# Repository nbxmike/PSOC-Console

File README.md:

# PSOC-Console

This is an expansion of the operator console for FIRST Robotic Competitions
originally published on the Cypress Semiconductor website:
  https://community.cypress.com/thread/30090
based on the CY8CKIT-059 development board.  I had previously released hardware
to ease the creation of the console, publised on the Cypress website:
  https://community.cypress.com/thread/30074
  
With this project, the Cypress GPL code is being replaced with MIT licensed 
firmware which runs as a task under FreeRTOS 10 (which is licensed under MIT
terms and hence the new firmware being released under the same license.)  The
firmware is not a port, it is new code which has at best been inspired by the
Cypress code meantioned above

The hardware is at the moment (11/OCT/2018) the same as was previously released
hardware.  A new revision of the hardware has been designed to incorporate a
3.3V regulator to make interfacing to PS/2, GameCube and other game console 
devices much easier.  It is entirely possible to interface the existing board
to 3.3V devices, and it has been done, it has been a painful kludge of wires
and ICs glued in place.  Expect updated hardware in the August 2018 timeframe
(boards are out for fab as I write.)

The project has been assigned the USB ID of 0x1d50 | 0x6131 by the 
openmoko USB OUI program.  Anticipating the hardware revision to 3.3V and its
associated updated firmware, a second ID is reserved.  Obtaining unique USB
IDs makes custom host support much easier should something other than stock
HID drivers be desired at some future point.

The project is broken down into three directories:
  Kicad - this folder includes the Kicad source files, gerbers, BOMs, etc.
    Kicad is a free schematic capture package the equal of many commercial
	packages but as FOSS it places no restrictions on use of its outputs.
  PSOC-Creator - This is the source for the firware and PLD of the CPU core
    used for this project.  PSOC Creator is a free integrated development
	enviroment which is not open source nor available for a package other than
	Windows.  It sucks that to use Cypress hardware you are forced into such
	a crap desktop but Cypress does not seem to care too much.
  Documents - I have collected a number for reference documents that I have
    included in this folder.  Should a copyright holder ask that I not provide
	people this information source I will attempt to find open documents to 
	replace them.
	
Licensing:
  Hardware - CERN
  Firmware - MIT
  Documents - individual terms are in each document
  
Enjoy

Mike

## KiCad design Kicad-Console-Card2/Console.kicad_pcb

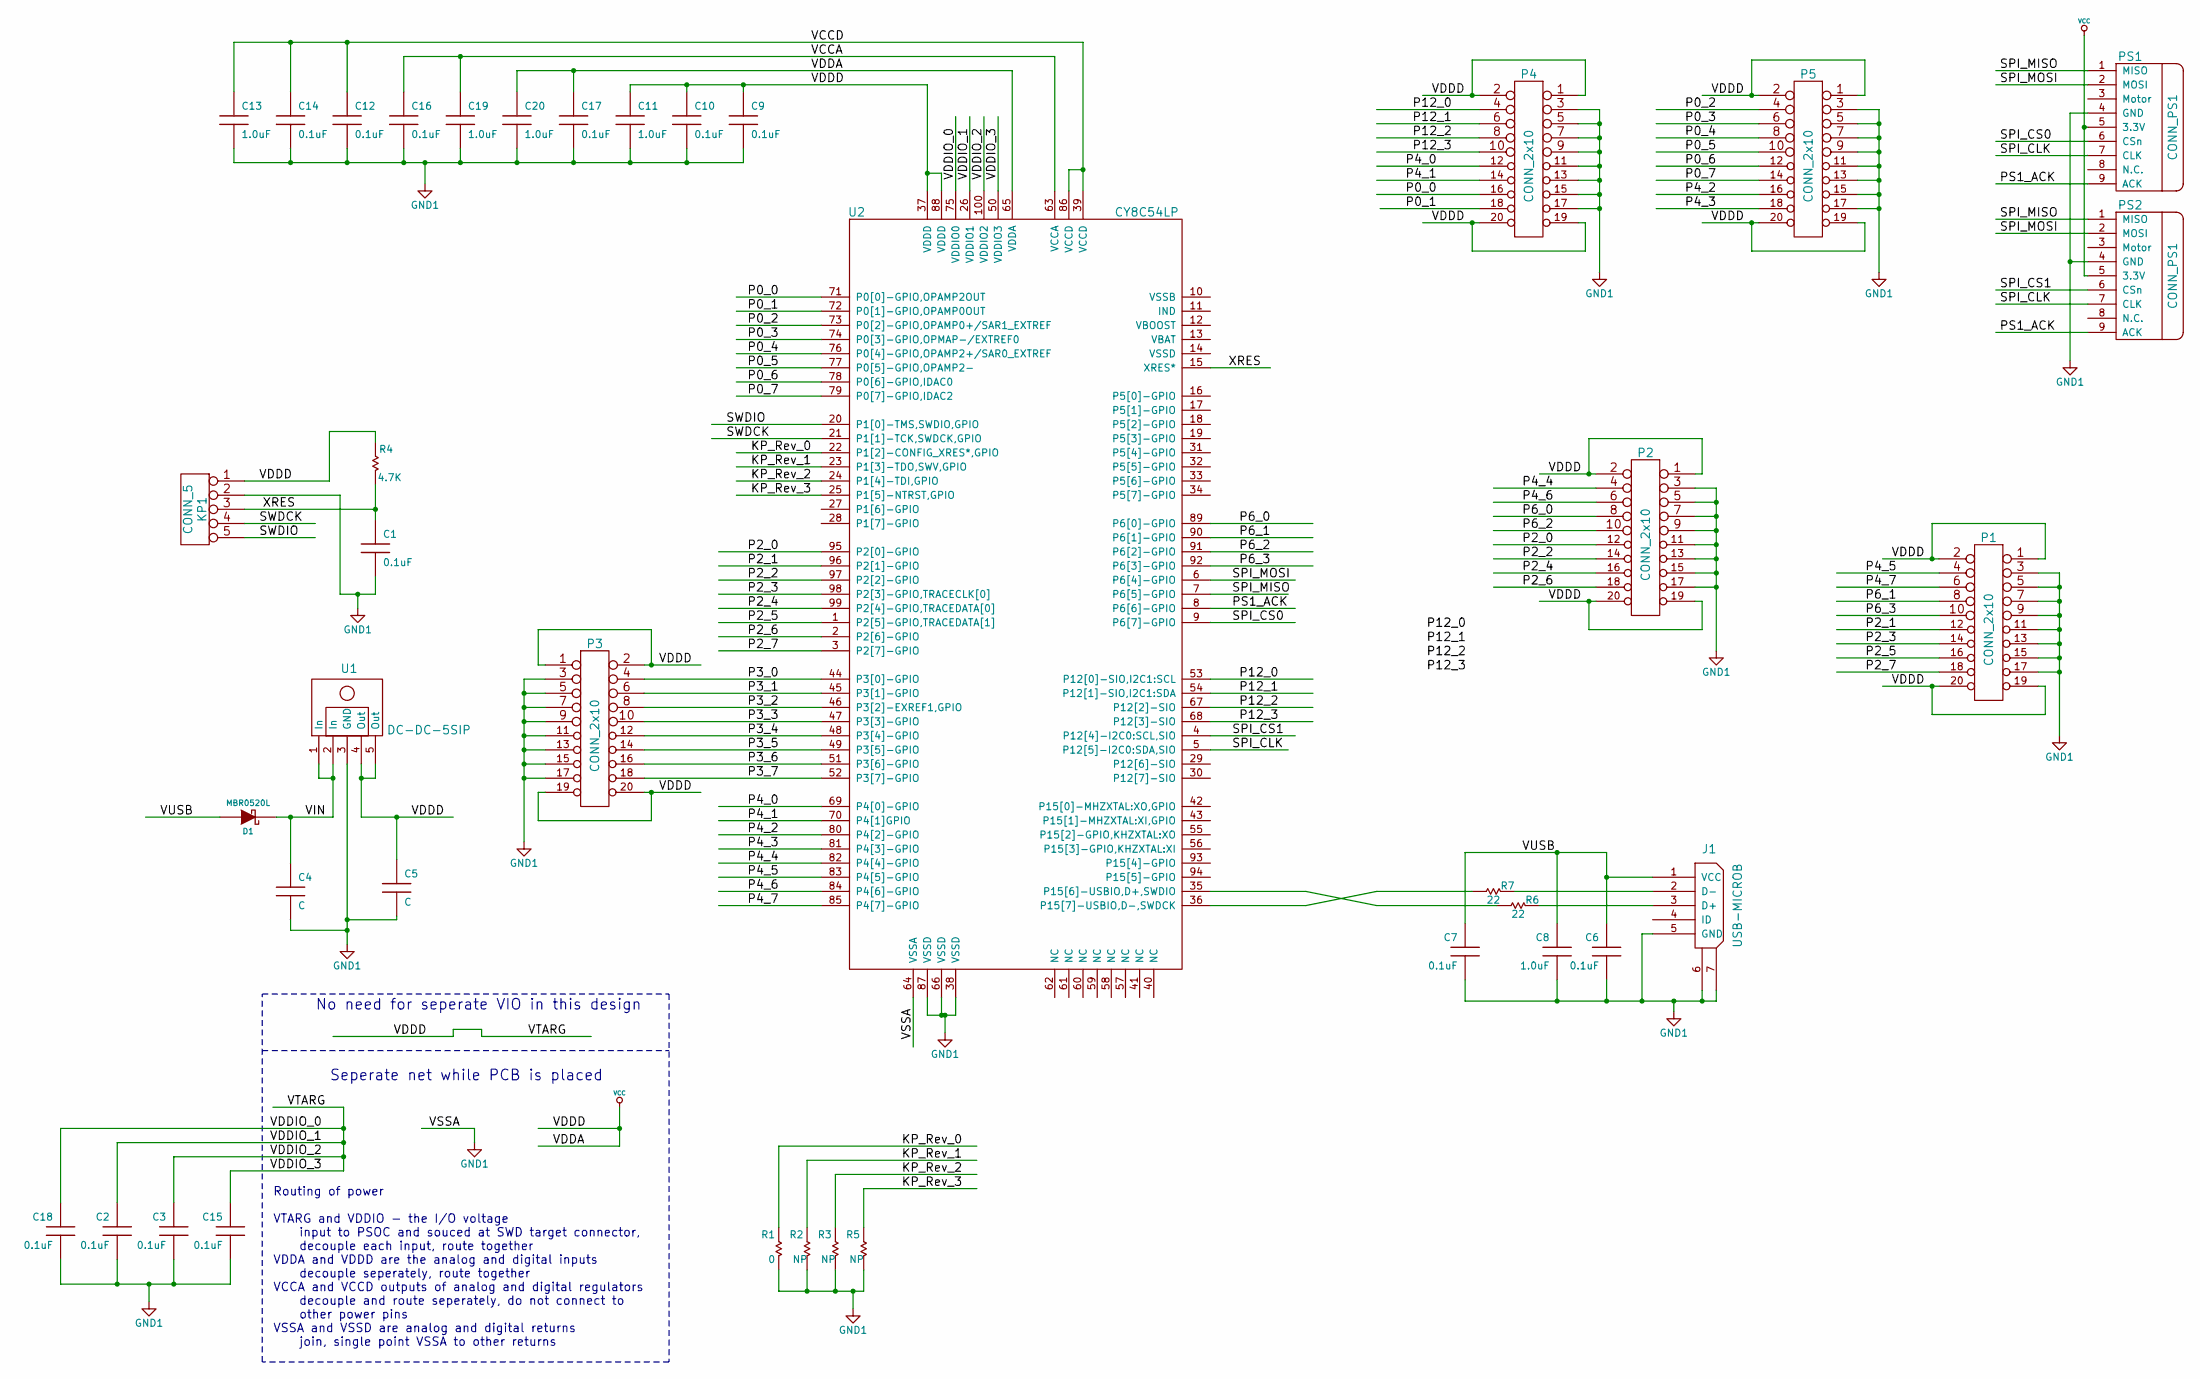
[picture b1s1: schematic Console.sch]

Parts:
C1, C2, C3, C6, C7, C9, C10, C12, C14, C15, C16, C17, C18: 0.1uF; c_0603
C4, C5: C; c_1210
C8, C11, C13, C19, C20: 1.0uF; c_0603
D1: MBR0520L; D_SOD-123
J1: USB-MICROB; Micro_usb_b
KP1: CONN_5; HEADER_1x05
P1, P2, P3, P4, P5: CONN_2x10; CONN_2_10
PS1, PS2: CONN_PS1; PS1-Ctrlr
R1: 0; JUMPER-SHORT
R2, R3, R5: NP; JUMPER-OPEN
R4: 4.7K; r_0603
R6, R7: 22; r_0603
U1: DC-DC-5SIP; DC-Custom5
U2: CY8C54LP; QFP_100

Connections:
/KP_Rev_0: R1.2, U2.22 (P1[2]-CONFIG_XRES*,GPIO)
/KP_Rev_1: R2.2, U2.23 (P1[3]-TDO,SWV,GPIO)
/KP_Rev_2: R3.2, U2.24 (P1[4]-TDI,GPIO)
/KP_Rev_3: R5.2, U2.25 (P1[5]-NTRST,GPIO)
/P0_0: P4.16, U2.71 (P0[0]-GPIO,OPAMP2OUT)
/P0_1: P4.18, U2.72 (P0[1]-GPIO,OPAMP0OUT)
/P0_2: P5.4, U2.73 (P0[2]-GPIO,OPAMP0+/SAR1_EXTREF)
/P0_3: P5.6, U2.74 (P0[3]-GPIO,OPMAP-/EXTREF0)
/P0_4: P5.8, U2.76 (P0[4]-GPIO,OPAMP2+/SAR0_EXTREF)
/P0_5: P5.10, U2.77 (P0[5]-GPIO,OPAMP2-)
/P0_6: P5.12, U2.78 (P0[6]-GPIO,IDAC0)
/P0_7: P5.14, U2.79 (P0[7]-GPIO,IDAC2)
/P2_0: P2.12, U2.95 (P2[0]-GPIO)
/P2_1: P1.12, U2.96 (P2[1]-GPIO)
/P2_2: P2.14, U2.97 (P2[2]-GPIO)
/P2_3: P1.14, U2.98 (P2[3]-GPIO,TRACECLK[0])
/P2_4: P2.16, U2.99 (P2[4]-GPIO,TRACEDATA[0])
/P2_5: P1.16, U2.1 (P2[5]-GPIO,TRACEDATA[1])
/P2_6: P2.18, U2.2 (P2[6]-GPIO)
/P2_7: P1.18, U2.3 (P2[7]-GPIO)
/P3_0: P3.4, U2.44 (P3[0]-GPIO)
/P3_1: P3.6, U2.45 (P3[1]-GPIO)
/P3_2: P3.8, U2.46 (P3[2]-EXREF1,GPIO)
/P3_3: P3.10, U2.47 (P3[3]-GPIO)
/P3_4: P3.12, U2.48 (P3[4]-GPIO)
/P3_5: P3.14, U2.49 (P3[5]-GPIO)
/P3_6: P3.16, U2.51 (P3[6]-GPIO)
/P3_7: P3.18, U2.52 (P3[7]-GPIO)
/P4_0: P4.12, U2.69 (P4[0]-GPIO)
/P4_1: P4.14, U2.70 (P4[1]GPIO)
/P4_2: P5.16, U2.80 (P4[2]-GPIO)
/P4_3: P5.18, U2.81 (P4[3]-GPIO)
/P4_4: P2.4, U2.82 (P4[4]-GPIO)
/P4_5: P1.4, U2.83 (P4[5]-GPIO)
/P4_6: P2.6, U2.84 (P4[6]-GPIO)
/P4_7: P1.6, U2.85 (P4[7]-GPIO)
/P6_0: P2.8, U2.89 (P6[0]-GPIO)
/P6_1: P1.8, U2.90 (P6[1]-GPIO)
/P6_2: P2.10, U2.91 (P6[2]-GPIO)
/P6_3: P1.10, U2.92 (P6[3]-GPIO)
/P12_0: P4.4, U2.53 (P12[0]-SIO,I2C1:SCL)
/P12_1: P4.6, U2.54 (P12[1]-SIO,I2C1:SDA)
/P12_2: P4.8, U2.67 (P12[2]-SIO)
/P12_3: P4.10, U2.68 (P12[3]-SIO)
/PS1_ACK: PS1.9 (ACK), PS2.9 (ACK), U2.8 (P6[6]-GPIO)
/SPI_CLK: PS1.7 (CLK), PS2.7 (CLK), U2.5 (P12[5]-I2C0:SDA,SIO)
/SPI_CS0: PS1.6 (CSn), U2.9 (P6[7]-GPIO)
/SPI_CS1: PS2.6 (CSn), U2.4 (P12[4]-I2C0:SCL,SIO)
/SPI_MISO: PS1.1 (MISO), PS2.1 (MISO), U2.7 (P6[5]-GPIO)
/SPI_MOSI: PS1.2 (MOSI), PS2.2 (MOSI), U2.6 (P6[4]-GPIO)
/SWDCK: KP1.4, U2.21 (P1[1]-TCK,SWDCK,GPIO)
/SWDIO: KP1.5, U2.20 (P1[0]-TMS,SWDIO,GPIO)
/VCCA: C16.1, C19.1, U2.63 (VCCA)
/VCCD: C12.1, C13.1, C14.1, U2.39 (VCCD), U2.86 (VCCD)
/VIN: C4.1, D1.1 (C), U1.1 (In), U1.2 (In)
/VUSB: C6.1, C7.1, C8.1, D1.2 (A), J1.1 (VCC)
/XRES: C1.1, KP1.3, R4.2, U2.15 (XRES*)
GND1: C1.2, C2.2, C3.2, C4.2, C5.2, C6.2, C7.2, C8.2, C9.2, C10.2, C11.2, C12.2, C13.2, C14.2, C15.2, C16.2, C17.2, C18.2, C19.2, C20.2, J1.5 (GND), J1.6, J1.7, KP1.2, P1.3, P1.5, P1.7, P1.9, P1.11, P1.13, P1.15, P1.17, P2.3, P2.5, P2.7, P2.9, P2.11, P2.13, P2.15, P2.17, P3.3, P3.5, P3.7, P3.9, P3.11, P3.13, P3.15, P3.17, P4.3, P4.5, P4.7, P4.9, P4.11, P4.13, P4.15, P4.17, P5.3, P5.5, P5.7, P5.9, P5.11, P5.13, P5.15, P5.17, PS1.4 (GND), PS2.4 (GND), R1.1, R2.1, R3.1, R5.1, U1.3 (GND), U2.38 (VSSD), U2.64 (VSSA), U2.66 (VSSD), U2.87 (VSSD)
unnamed: J1.2 (D-), R7.1
unnamed: J1.3 (D+), R6.1
unnamed: R6.2, U2.35 (P15[6]-USBIO,D+,SWDIO)
unnamed: R7.2, U2.36 (P15[7]-USBIO,D-,SWDCK)
VCC: C2.1, C3.1, C5.1, C9.1, C10.1, C11.1, C15.1, C17.1, C18.1, C20.1, KP1.1, P1.1, P1.2, P1.19, P1.20, P2.1, P2.2, P2.19, P2.20, P3.1, P3.2, P3.19, P3.20, P4.1, P4.2, P4.19, P4.20, P5.1, P5.2, P5.19, P5.20, PS1.5 (3.3V), PS2.5 (3.3V), R4.1, U1.4 (Out), U1.5 (Out), U2.26 (VDDIO1), U2.37 (VDDD), U2.50 (VDDIO3), U2.65 (VDDA), U2.75 (VDDIO0), U2.88 (VDDD), U2.100 (VDDIO2)

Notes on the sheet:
Seperate net while PCB is placed
Routing of power VTARG and VDDIO - the I/O voltage input to PSOC and souced at SWD target connector, decouple each input, route together VDDA and VDDD are the analog and digital inputs decouple seperately, route together VCCA and VCCD outputs of analog and digital regulators decouple and route sepe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
No need for seperate VIO in this design

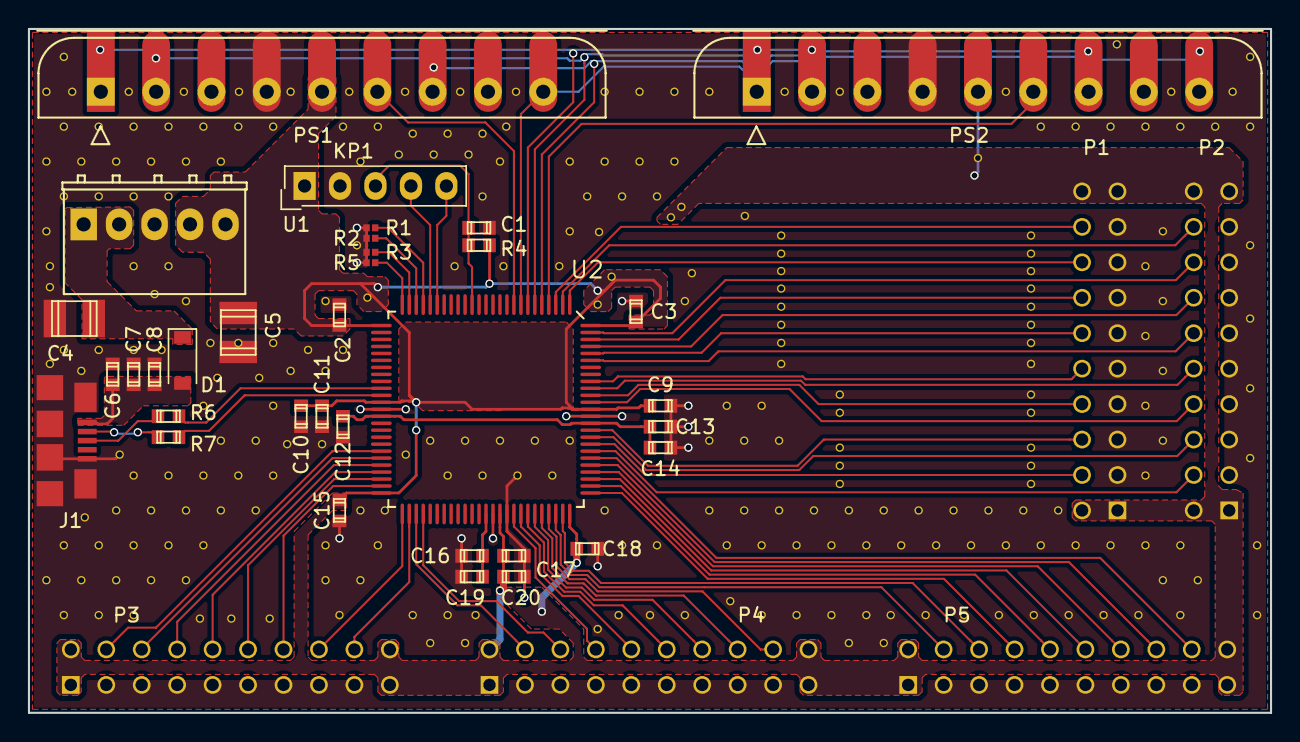
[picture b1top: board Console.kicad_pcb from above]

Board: 2 copper layers, 89.0 x 49.0 mm, 39 parts (0 on the bottom side), 63 nets.

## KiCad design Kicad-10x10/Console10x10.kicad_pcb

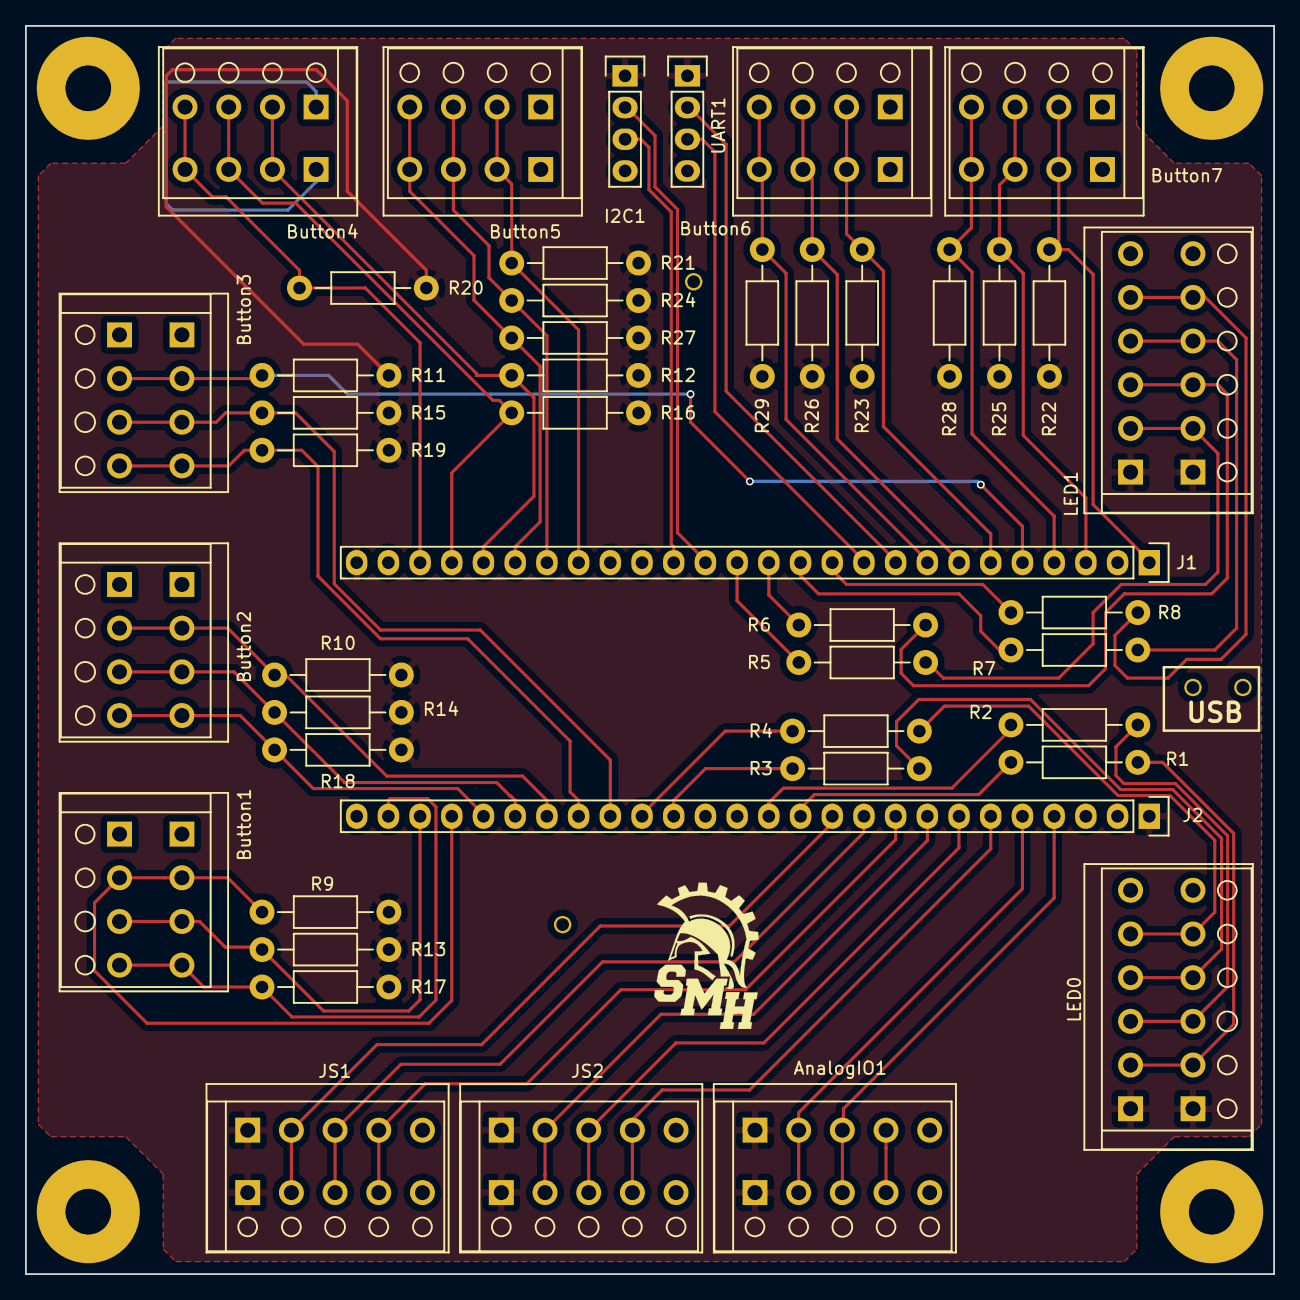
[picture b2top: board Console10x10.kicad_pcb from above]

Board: 2 copper layers, 100.0 x 100.0 mm, 55 parts (1 on the bottom side), 51 nets.

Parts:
AnalogIO1: CONN_01X05; PTSA-5
B1, B2, B3, B4: HOLE; MH-No6-3p5
Button1, Button2, Button3, Button4, Button5, Button6, Button7: CONN_01X04; PTSA-4
I2C1: CONN_01X04; Pin_Header_Straight_1x04
J1, J2: CONN_01X26; Pin_Header_Straight_1x26
JS1, JS2: CONN_01X05; PTSA-5
LED0, LED1: CONN_01X06; PTSA-6
Logo1: LOGO; StMarySmall
Logo2: LOGO; StMaryLarge
R1, R2, R3, R4, R5, R6, R7, R8: 330; Resistor_Horizontal_RM10mm
R9, R10, R11, R12, R13, R14, R15, R16, R17, R18, R19, R20, R21, R22, R23, R24, R25, R26, R27, R28, R29: 4.7K; Resistor_Horizontal_RM10mm
T1, T2, T3, T4: TP; TP-TH
UART1: CONN_01X04; Pin_Header_Straight_1x04

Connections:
/GND: AnalogIO1.5, Button1.1, Button2.1, Button3.1, Button4.1, Button5.1, Button6.1, Button7.1, I2C1.4, J1.25, J2.2, J2.26, JS1.5, JS2.5, LED0.6, LED1.6, T1.1, T2.1, T3.1, T4.1, UART1.4
/P0.0: J2.11, JS1.2
/P0.1: J2.10, JS1.3
/P0.2: J2.9, JS1.4
/P0.3: J2.8, JS2.2
/P0.4: J2.7, JS2.3
/P0.5: J2.6, JS2.4
/P0.6: AnalogIO1.2, J2.5
/P0.7: AnalogIO1.3, J2.4
/P1.2: Button5.2, J1.19, R21.2
/P1.3: Button5.3, J1.20, R24.2
/P1.4: Button5.4, J1.21, R27.2
/P1.5: Button4.2, J1.22, R12.2
/P1.6: Button4.3, J1.23, R16.2
/P1.7: Button4.4, J1.24, R20.2
/P2.0: Button7.2, J1.1, R22.2
/P2.2: Button7.3, J1.3, R25.2
/P2.3: Button7.4, J1.4, R28.2
/P2.4: Button3.2, J1.5, R11.2
/P2.5: Button6.2, J1.6, R23.2
/P2.6: Button6.3, J1.7, R26.2
/P2.7: Button6.4, J1.8, R29.2
/P3.0: Button1.4, J2.25, R17.2
/P3.1: Button1.3, J2.24, R13.2
/P3.2: Button1.2, J2.23, R9.2
/P3.3: Button2.4, J2.22, R18.2
/P3.4: Button2.3, J2.21, R14.2
/P3.5: Button2.2, J2.20, R10.2
/P3.6: Button3.4, J2.19, R19.2
/P3.7: Button3.3, J2.18, R15.2
/P12.2: J1.14, R5.1
/P12.3: J1.13, R6.1
/P12.4: J1.12, R7.1
/P12.5: J1.11, R8.1
/P15.0: J2.17, R4.1
/P15.1: J2.16, R3.1
/P15.4: J2.13, R2.1
/P15.5: J2.12, R1.1
/RCV: J1.10, UART1.3
/SCL: I2C1.3, J1.16
/SDA: I2C1.2, J1.15
/TXD: J1.9, UART1.2
/VDD: AnalogIO1.1, I2C1.1, J1.26, J2.1, JS1.1, JS2.1, LED0.1, LED1.1, R9.1, R10.1, R11.1, R12.1, R13.1, R14.1, R15.1, R16.1, R17.1, R18.1, R19.1, R20.1, R21.1, R22.1, R23.1, R24.1, R25.1, R26.1, R27.1, R28.1, R29.1, UART1.1
unnamed: LED0.2, R1.2
unnamed: LED0.3, R2.2
unnamed: LED0.4, R3.2
unnamed: LED0.5, R4.2
unnamed: LED1.2, R5.2
unnamed: LED1.3, R6.2
unnamed: LED1.4, R7.2
unnamed: LED1.5, R8.2

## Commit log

2018-04-19 Initial distribution
2018-06-11 proper CERN license
2018-06-11 Reorganization for software and hardware
2018-06-12 Updates to licenses
2018-06-14 Revised README with more useful information
2018-09-16 PSx Sniifer cleaned up
2018-10-11 Mostly ready for FreeRTOS
2018-10-14 Updates to support shared USB
2018-11-02 Doxygen and USB fixes
2018-11-02 Straighten out the Docs
2018-11-13 Handle more error
2018-11-15 Moved to generic joystick data structure
2021-05-31 Just changes from updating the Cypress tools
2021-05-31 Adding documentation scattered across the web to the project foldes
2021-06-01 Kicad updates for new Kicad file systems-formats
2021-06-01 Mini dual PS2 console adapter added to the project
2021-06-25 Updating the sniffer reciever to Python 3.x
2021-06-25 Updating the sniffer reciever to Python 3.x, for real
2021-06-25 Changes cause by update to PSOC Creator
2021-06-30 Updates to documentation and FreeRTOS 10.4 mainly
2021-07-09 More updates related to FreeRTOS changes
2021-07-09 FreeRTOS CLI updates
2021-07-09 Playing with idicators outputs
2021-07-19 Changes to the output bits for use with LEDs
2021-07-26 Improved UI library (LEDs)
2022-04-03 update to FreeRTOS latest release and clang rules too
2022-04-03 Minor clean ups and format changes while adjusting clang
2022-04-03 Added a missing doc
